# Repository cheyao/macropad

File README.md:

# Macropad
Hello! This is my first time designing a PCB and a CAD.

Designed using:

- KiCad - Made a ton of revisions
- OpenSCAD then FreeCAD (Fusion 360 doesn't work on my mac lol) Got like 400 constraints in my freecad project
- Python firmware

## BOM
- 1 SEEEDUINO XIAO RP2040
- 16x [Kailh Choc V2 switches](https://www.kailh.net/products/kailh-choc-v2-low-profile-switch-set)
- 16x 1N4148 diodes
- 1x SSD1306 128x64O LED (5V VCC, 3.3V logic, I2C)
- 4x [SK6812-MINI-E LED](https://www.adafruit.com/product/4960)
- 2x 4.7k resistor
- 4x 0.1 uF capacitor (code 104, not obligatory but best have)
- 1x 1 uF capacitor (105 not obligatory)
- 4x same screws as orpheuspad and corresponding nuts
- 1kg of 99.99% gold please UwU

Interactive bom at `PCB/production/ibom.html`

## File list:

```
.
├── CAD                                         # 3D Files
│   ├── case.FCStd                              # Case FreeCAD design file
│   └── case.stl                                # Case stl output (Acrylic top if < 1.5mm thickness please)
├── PCB
│   ├── macropad.step                           # 3D Model of the board
│   ├── production                              # The output directory for production (Just send this folder to JLCPCB)
│   │   ├── Cyao_macropad_v7.6.zip              # Gerbers
│   │   ├── *.{csv,ipc}                         # Misc files for JLCPCB
│   │   └── ibom.html                           # Interactive bom for PCBAlex <3
│   └── third_party                             # 3rd party libraries
│       ├── Kalih                               # The keys
│       ├── OPL_Kicad_Library                   # Seed footprint
│       ├── KiCad-SSD1306-128x64-master         # LCD
│       └── Seeeduino-xiao-rp2040-KiCAD-Library # Seed schema
└── firmware                                    # Directory of my own firmware
    ├── adafruit-circuitpython-seeeduino_xiao_rp2040-en_US-9.1.4.uf2 # Circuitpython firmware
    ├── main.py                                 # Main firmware
    ├── boot.py                                 # Boot options (empty)
    └── kmk                                     # kmk firmware
```

NOTE: I will need a 0.96” SSD1306 OLED screen that accepts 5V with 3.3V logic

The resistors are allso probably optional - but suggested by reddit

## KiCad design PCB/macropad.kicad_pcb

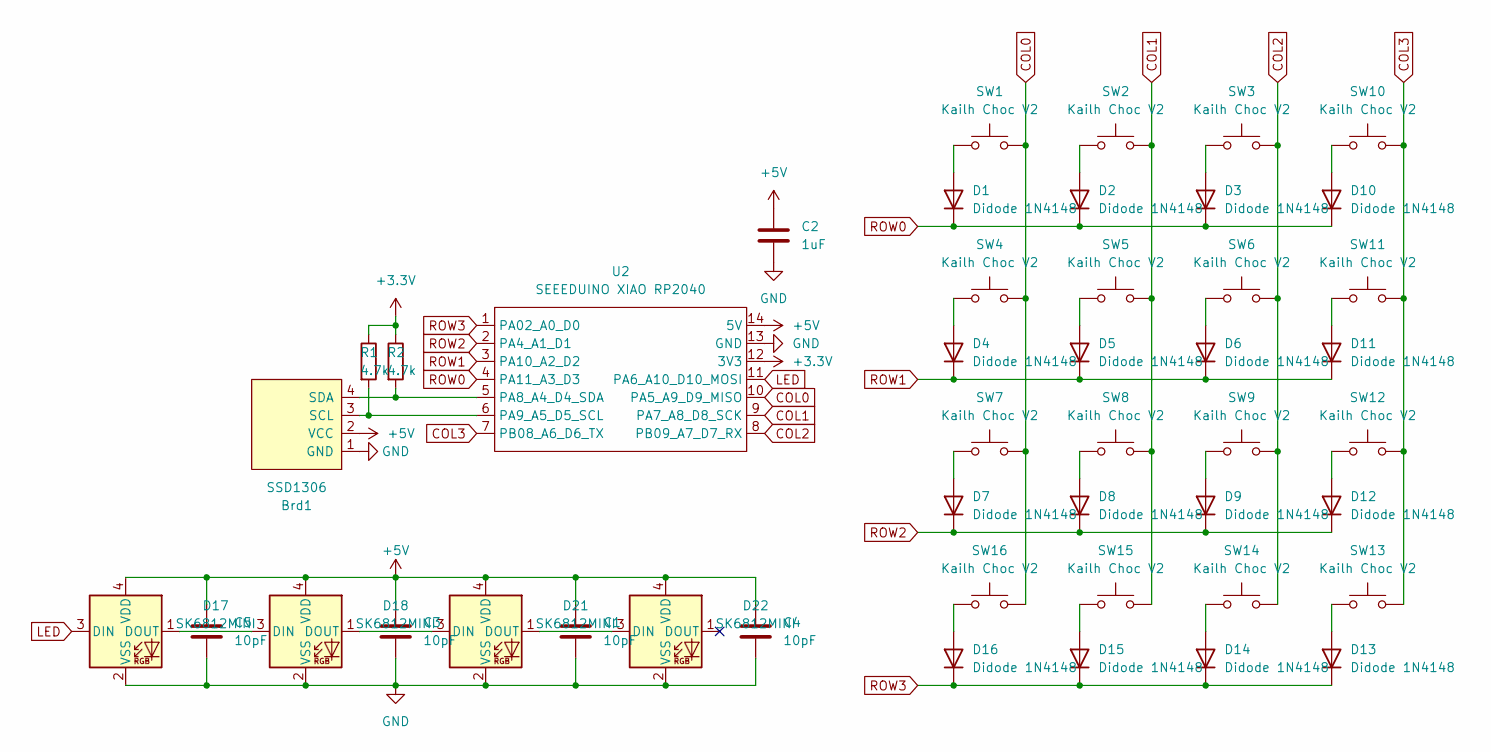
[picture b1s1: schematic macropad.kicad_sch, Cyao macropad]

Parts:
Brd1: SSD1306; 128x64OLED
C1, C3, C4, C5: 10pF; C_Disc_D3.0mm_W1.6mm_P2.50mm
C2: 1uF; C_Disc_D3.0mm_W1.6mm_P2.50mm
D1, D2, D3, D4, D5, D6, D7, D8, D9, D10, D11, D12, D13, D14, D15, D16: Didode 1N4148; D_DO-35_SOD27_P7.62mm_Horizontal
D17, D18, D21, D22: SK6812MINI; SK6812MINI-E
R1, R2: 4.7k; R_Axial_DIN0204_L3.6mm_D1.6mm_P7.62mm_Horizontal
SW1, SW2, SW3, SW4, SW5, SW6, SW7, SW8, SW9, SW10, SW11, SW12, SW13, SW14, SW15, SW16: Kailh Choc V2; SW_Kailh_Choc_V2_1.00u
U2: SEEEDUINO XIAO RP2040; XIAO-Generic-Hybrid-14P-2.54-21X17.8MM

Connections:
+3.3V: R1.1, R2.1, U2.12 (3V3)
+5V: Brd1.2 (VCC), C1.1, C2.1, C3.1, C4.1, C5.1, D17.4 (VDD), D18.4 (VDD), D21.4 (VDD), D22.4 (VDD), U2.14 (5V)
COL0: SW1.2, SW4.2, SW7.2, SW16.2, U2.10 (PA5_A9_D9_MISO)
COL1: SW2.2, SW5.2, SW8.2, SW15.2, U2.9 (PA7_A8_D8_SCK)
COL2: SW3.2, SW6.2, SW9.2, SW14.2, U2.8 (PB09_A7_D7_RX)
COL3: SW10.2, SW11.2, SW12.2, SW13.2, U2.7 (PB08_A6_D6_TX)
GND: Brd1.1 (GND), C1.2, C2.2, C3.2, C4.2, C5.2, D17.2 (VSS), D18.2 (VSS), D21.2 (VSS), D22.2 (VSS), U2.13 (GND)
LED: D17.3 (DIN), U2.11 (PA6_A10_D10_MOSI)
unnamed: Brd1.3 (SCL), R1.2, U2.6 (PA9_A5_D5_SCL)
unnamed: Brd1.4 (SDA), R2.2, U2.5 (PA8_A4_D4_SDA)
unnamed: D1.2 (A), SW1.1
unnamed: D2.2 (A), SW2.1
unnamed: D3.2 (A), SW3.1
unnamed: D4.2 (A), SW4.1
unnamed: D5.2 (A), SW5.1
unnamed: D6.2 (A), SW6.1
unnamed: D7.2 (A), SW7.1
unnamed: D8.2 (A), SW8.1
unnamed: D9.2 (A), SW9.1
unnamed: D10.2 (A), SW10.1
unnamed: D11.2 (A), SW11.1
unnamed: D12.2 (A), SW12.1
unnamed: D13.2 (A), SW13.1
unnamed: D14.2 (A), SW14.1
unnamed: D15.2 (A), SW15.1
unnamed: D16.2 (A), SW16.1
unnamed: D17.1 (DOUT), D18.3 (DIN)
unnamed: D18.1 (DOUT), D21.3 (DIN)
unnamed: D21.1 (DOUT), D22.3 (DIN)
ROW0: D1.1 (K), D2.1 (K), D3.1 (K), D10.1 (K), U2.4 (PA11_A3_D3)
ROW1: D4.1 (K), D5.1 (K), D6.1 (K), D11.1 (K), U2.3 (PA10_A2_D2)
ROW2: D7.1 (K), D8.1 (K), D9.1 (K), D12.1 (K), U2.2 (PA4_A1_D1)
ROW3: D13.1 (K), D14.1 (K), D15.1 (K), D16.1 (K), U2.1 (PA02_A0_D0)

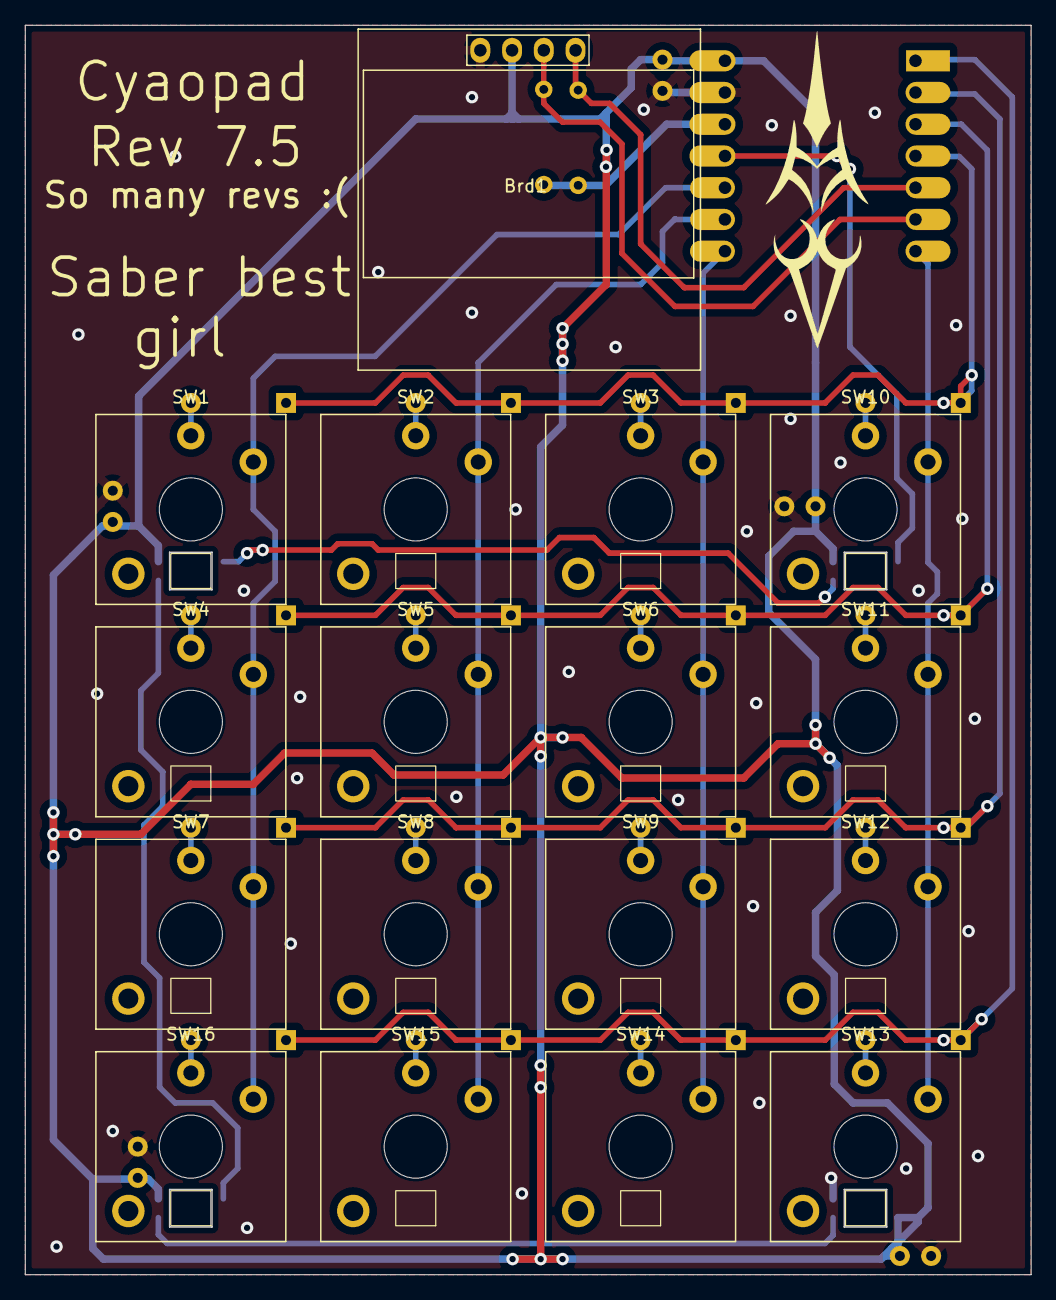
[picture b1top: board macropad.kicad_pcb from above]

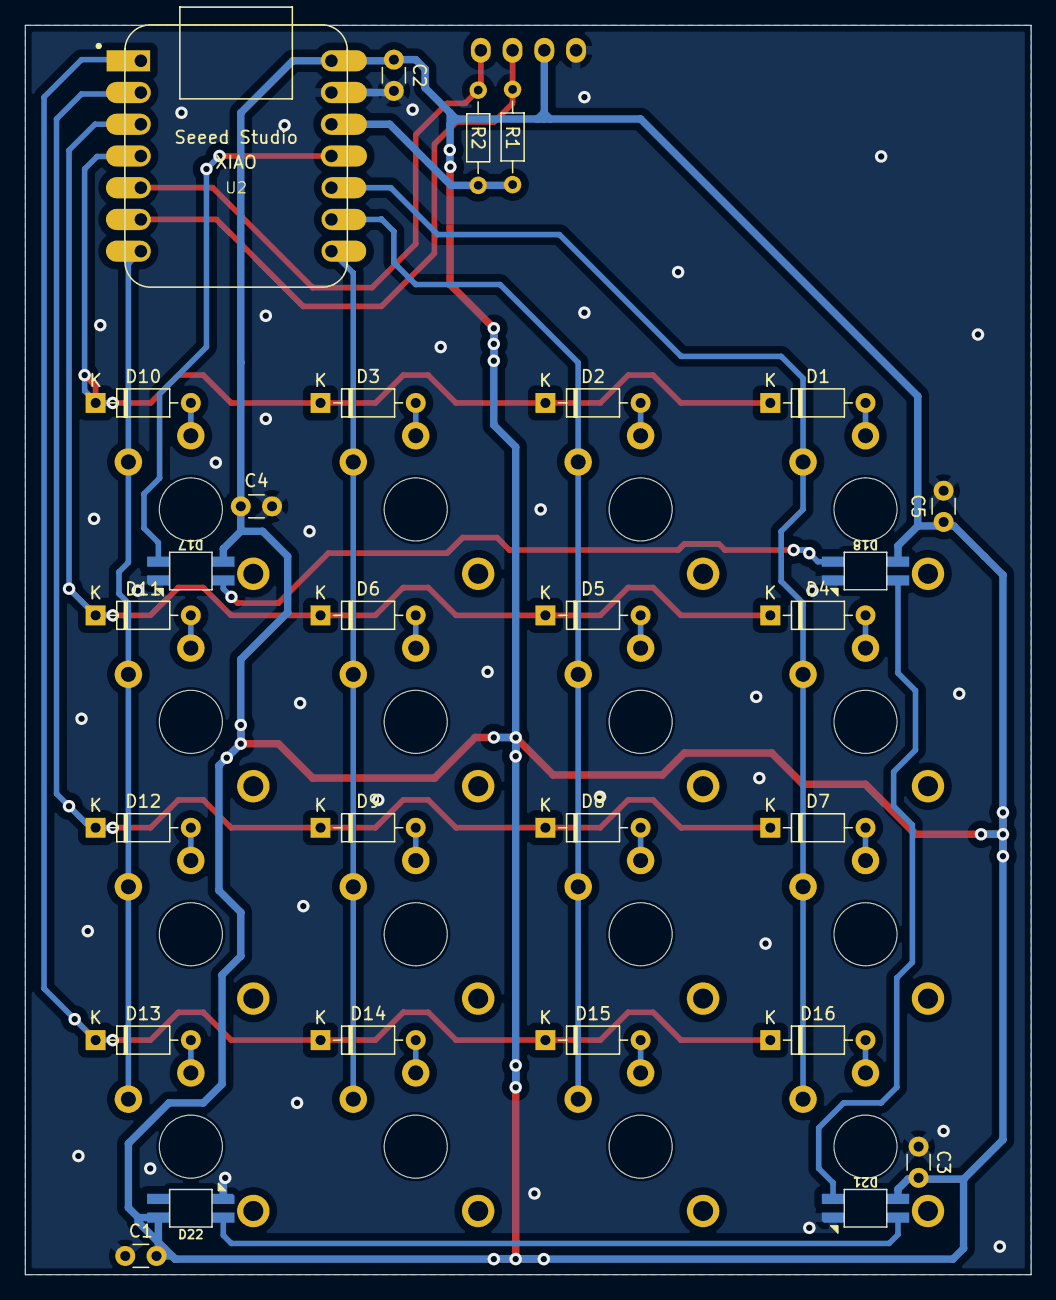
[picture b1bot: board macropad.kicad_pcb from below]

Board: 2 copper layers, 80.5 x 100.0 mm, 45 parts (28 on the bottom side), 33 nets.

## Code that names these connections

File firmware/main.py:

# Cyao macropad firmware
# Rev 1.1
# Copyright 2024
# Licensed under zlib license
import board
import busio
import time
import board
from rainbowio import colorwheel

from kmk.kmk_keyboard import KMKKeyboard
from kmk.keys import KC
from kmk.scanners import DiodeOrientation
from kmk.modules.macros import Macros
from kmk.extensions.display import Display, TextEntry, ImageEntry
from kmk.extensions.display.ssd1306 import SSD1306
from kmk.extensions.RGB import RGB
from kmk.extensions.rgb import AnimationModes

COL0 = board.D9;
COL1 = board.D8;
COL2 = board.D7;
COL3 = board.D6;
ROW0 = board.D3;
ROW1 = board.D2;
ROW2 = board.D1;
ROW3 = board.D0;

LED_PIN = board.D10;

bus = busio.I2C(board.SCL, board.SDA);

driver = SSD1306(i2c=bus, device_address=0x3C);

display = Display(
    display=driver,
    width=128,
    height=64,
    dim_time=10,
    dim_target=0.2,
    off_time=1200,
    brightness=0.7
);

display.entries = [
    ImageEntry(image="pic.bmp", x=0, y=0),
];

keyboard = KMKKeyboard();

macros = Macros();
keyboard.modules.append(macros);
keyboard.extensions.append(display);

keyboard.col_pins = (COL0, COL1, COL2, COL3);
keyboard.row_pins = (ROW0, ROW1, ROW2, ROW3);
keyboard.diode_orientation = DiodeOrientation.COL2ROW;

rgb = RGB(pixel_pin=board.D10, num_pixels=4, animation_speed=1, animation_mode=AnimationModes.SWIRL)
keyboard.extensions.append(rgb)

from kmk.modules.macros import Press, Release, Tap, Delay
from kmk.modules.mouse_keys import MouseKeys
keyboard.modules.append(MouseKeys())

A = KC.MACRO(
    Press(KC.LCMD),
    Tap(KC.T),
    Release(KC.LCMD)
);
B = KC.MACRO(
    Press(KC.LALT),
    Tap(KC.T),
    Release(KC.LALT)
);
C = KC.MACRO(
    Press(KC.LALT),
    Tap(KC.W),
    Release(KC.LALT)
);
D = KC.MACRO(
    Press(KC.LCMD),
    Tap(KC.Q),
    Release(KC.LCMD)
);

E = KC.MS_LT;
F = KC.MS_DN;
G = KC.MS_UP;
H = KC.MS_RT;

I = KC.MW_DN;
J = KC.MW_UP;
K = KC.MACRO(
    Press(KC.LCMD),
    Press(KC.LSFT),
    Tap(KC.F),
    Release(KC.LCMD),
    Release(KC.LSFT),
);
L = KC.LALT;

M = KC.MB_LMB;
N = KC.MB_RMB;
O = KC.MACRO(
    Press(KC.LCMD),
    Tap(KC.LEFT),
    Release(KC.LCMD)
);
P = KC.MACRO(
    Press(KC.LCMD),
    Tap(KC.RIGHT),
    Release(KC.LCMD)
);

keyboard.keymap = [
    [A, B, C, D,
     E, F, G, H,
     I, J, K, L,
     M, N, O, P],
];

if __name__ == '__main__':
    keyboard.go();

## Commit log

2024-09-12 Init
2024-09-12 Save, half-finished schematic, start of PCB
2024-09-13 Finish first state of PCB
2024-09-14 Improved PCB
2024-09-14 Start of firmware
2024-09-14 Firmware
2024-09-14 Start of case
2024-09-14 Mis of case
2024-09-14 Cover
2024-09-14 Finish Case
2024-09-15 Finish macropad
2024-09-15 Fix stuff
2024-09-15 Dir listing
2024-09-19 Silkscreen
2024-09-20 LCD!
2024-09-20 Finish
2024-09-20 Improve README
2024-09-21 Add step & stl for PCB
2024-09-22 Add 3D models
2024-09-22 Increase cover keypad hole size
2024-09-22 Add file names, clean up designators & Improve output
2024-09-22 Fix .gitignore
2024-09-22 Fix pads
2024-09-22 Added 3D model for xiao
2024-09-22 Fix CAD usb hole alignment
2024-09-22 Add pullup resistors for I2C
2024-09-23 Moved diodes
2024-09-23 Add plate and use insert for case
2024-09-24 Change side of tracks connecting to keys
2024-09-25 Misc improvements
2024-09-26 Use thru-hole xiao
2024-10-03 Redisigned PCB
2024-10-05 Revamped switch footprints and routing
2024-10-06 Add LEDs to PCB
2024-10-06 Add case
2024-10-06 Finish firmware + misc updates
2024-10-07 Add BOM in readme
2024-10-08 Add decoupling capacitors & verified footprints
2024-10-08 Revamp switch margins
2024-10-08 Adapt case to new switch margins
2024-10-09 Added backlights
2024-10-09 Add silkscreens and misc improvements
2024-10-10 Firmware path + clean up tracks
2024-10-15 Sync
2024-10-16 Change capacitor values and positions
2024-10-17 Follow best practices and use stiching vias
2024-10-17 Add slope to case
2024-10-20 Final revision
2024-10-21 Sync with the hackpad
2025-01-09 Fix firmware
2025-02-09 Add some 3d models
